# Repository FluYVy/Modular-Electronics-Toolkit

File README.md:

# Modular-Electronics-Toolkit

This project is a diploma thesis done at the [HTL Rankweil](https://github.com/htl-rankweil). It aims to provide future students with a better way to understand and work with different sensors and actuators. The system created aims to be modular so that different parts of it can be mixed to create new and creative projects. Different libraries are also provided to help students use these modules.

To further help with the development of different projects, a visual coding engine can be used to create the needed code. This is done with [Blockly](https://developers.google.com/blockly), which was developed by Google.

## Key Features
### Compability
The modules created should be compatible with any microcontroller, as long as they can handle 5 volts.

> [!WARNING]
> The provided code and libraries have only been tested with a board using the ATMEGA16A-Chip. For other microcontrollers, you may need to create your own code.

### Modular
The modules are designed to be able to create new projects by combining them together. As such, even complex problems can be solved easily.

### Easy to use
The libraries are designed to be used by students and as such are easy to use and adapt to your project or solution. This is reinforced by the block-based code editor for easy project creation. 

## Used Software and Libraries
* [Microchip Studio](https://www.microchip.com/en-us/tools-resources/develop/microchip-studio) for programming the libraries
* [KiCad](https://www.kicad.org/) for creating the modules
* [Blockly](https://developers.google.com/blockly) as a library for the blocks-based code editor

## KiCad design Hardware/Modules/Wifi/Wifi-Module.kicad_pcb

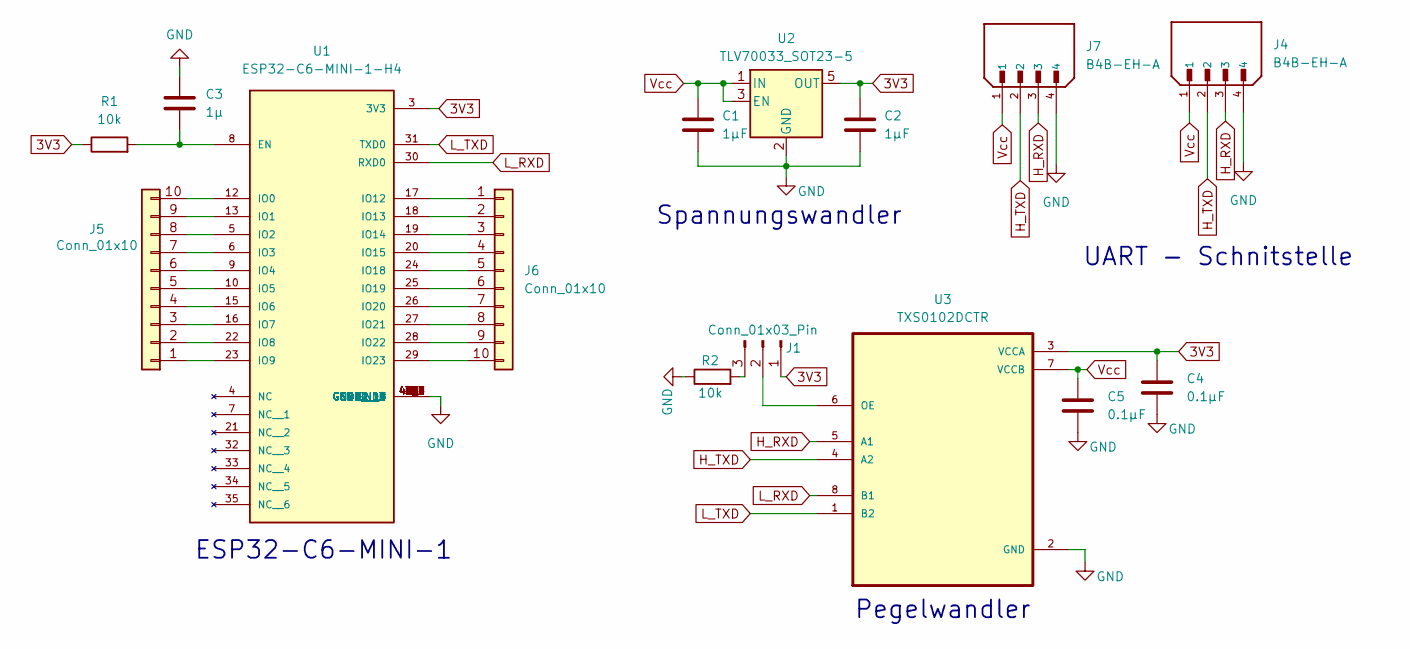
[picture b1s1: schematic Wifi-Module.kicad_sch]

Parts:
C1, C2: 1µF; C_0603_1608Metric_Pad1.08x0.95mm_HandSolder
C3: 1µ; C_0603_1608Metric_Pad1.08x0.95mm_HandSolder
C4, C5: 0.1µF; C_0603_1608Metric_Pad1.08x0.95mm_HandSolder
J1: Conn_01x03_Pin; PinHeader_1x03_P2.54mm_Vertical
J4, J7: B4B-EH-A; JST_B4B-EH-A
J5, J6: Conn_01x10; PinHeader_1x10_P2.54mm_Vertical
R1, R2: 10k; R_0603_1608Metric_Pad0.98x0.95mm_HandSolder
U1: ESP32-C6-MINI-1-H4; XCVR_ESP32-C6-MINI-1-H4; PARTREV 1.0
U2: TLV70033_SOT23-5; SOT-23-5
U3: TXS0102DCTR

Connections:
3V3: C2.1, C4.2, J1.1, R1.1, U1.3 (3V3), U2.5 (OUT), U3.3 (VCCA)
GND: C1.2, C2.2, C3.1, C4.1, C5.1, J4.4, J7.4, R2.1, U1.1 (GND1), U1.2 (GND1__1), U1.11 (GND1__2), U1.14 (GND1__3), U1.36 (GND1__4), U1.37 (GND1__5), U1.38 (GND1__6), U1.39 (GND1__7), U1.40 (GND1__8), U1.41 (GND1__9), U1.42 (GND1__10), U1.43 (GND1__11), U1.44 (GND1__12), U1.45 (GND1__13), U1.46 (GND1__14), U1.47 (GND2), U1.48 (GND2__1), U1.49_1 (GND2__2), U1.49_2 (GND2__3), U1.49_3 (GND2__4), U1.49_4 (GND2__5), U1.49_5 (GND2__6), U1.49_6 (GND2__7), U1.49_7 (GND2__8), U1.49_8 (GND2__9), U1.49_9 (GND2__10), U1.50 (GND2__11), U1.51 (GND2__12), U1.52 (GND2__13), U1.53 (GND2__14), U2.2 (GND), U3.2 (GND)
H_RXD: J4.3, J7.3, U3.5 (A1)
H_TXD: J4.2, J7.2, U3.4 (A2)
L_RXD: U1.30 (RXD0), U3.8 (B1)
L_TXD: U1.31 (TXD0), U3.1 (B2)
unnamed: J1.2, U3.6 (OE)
unnamed: J1.3, R2.2
unnamed: J5.1, U1.23 (IO9)
unnamed: J5.2, U1.22 (IO8)
unnamed: J5.3, U1.16 (IO7)
unnamed: J5.4, U1.15 (IO6)
unnamed: J5.5, U1.10 (IO5)
unnamed: J5.6, U1.9 (IO4)
unnamed: J5.7, U1.6 (IO3)
unnamed: J5.8, U1.5 (IO2)
unnamed: J5.9, U1.13 (IO1)
unnamed: J5.10, U1.12 (IO0)
unnamed: J6.1, U1.17 (IO12)
unnamed: J6.2, U1.18 (IO13)
unnamed: J6.3, U1.19 (IO14)
unnamed: J6.4, U1.20 (IO15)
unnamed: J6.5, U1.24 (IO18)
unnamed: J6.6, U1.25 (IO19)
unnamed: J6.7, U1.26 (IO20)
unnamed: J6.8, U1.27 (IO21)
unnamed: J6.9, U1.28 (IO22)
unnamed: J6.10, U1.29 (IO23)
unnamed: C3.2, R1.2, U1.8 (EN)
Vcc: C1.1, C5.2, J4.1, J7.1, U2.1 (IN), U2.3 (EN), U3.7 (VCCB)

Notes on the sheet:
UART - Schnitstelle
ESP32-C6-MINI-1
Pegelwandler
Spannungswandler

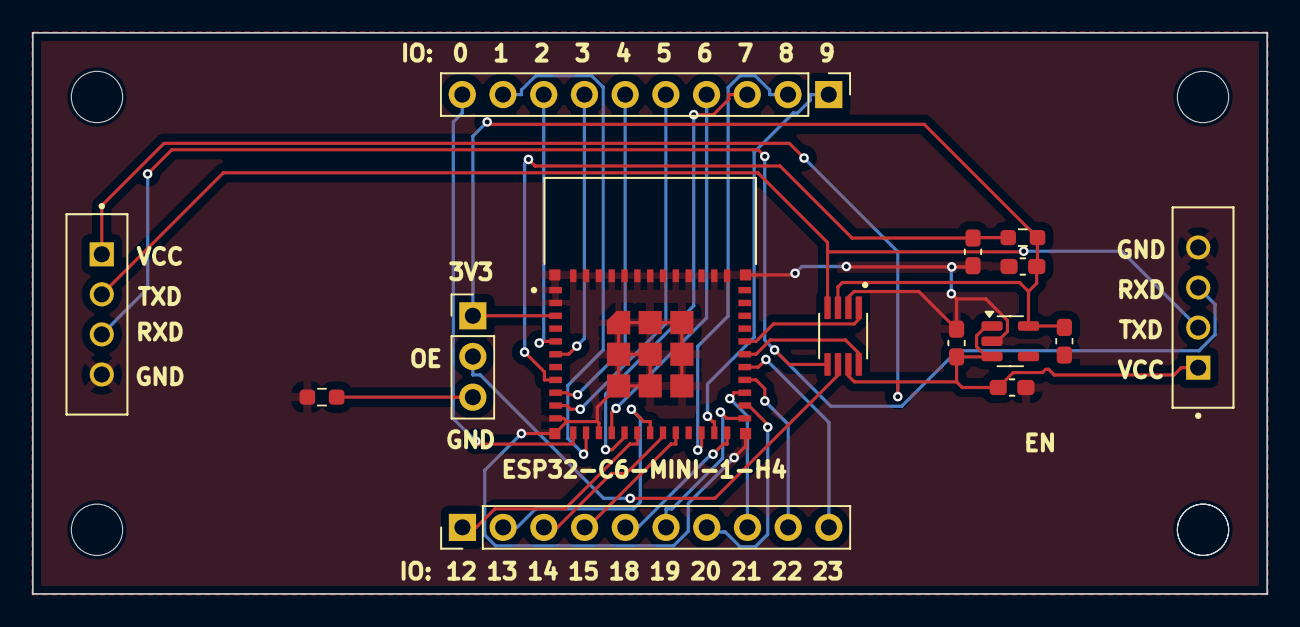
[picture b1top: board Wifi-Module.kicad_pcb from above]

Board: 2 copper layers, 77.0 x 35.0 mm, 15 parts (0 on the bottom side), 30 nets.

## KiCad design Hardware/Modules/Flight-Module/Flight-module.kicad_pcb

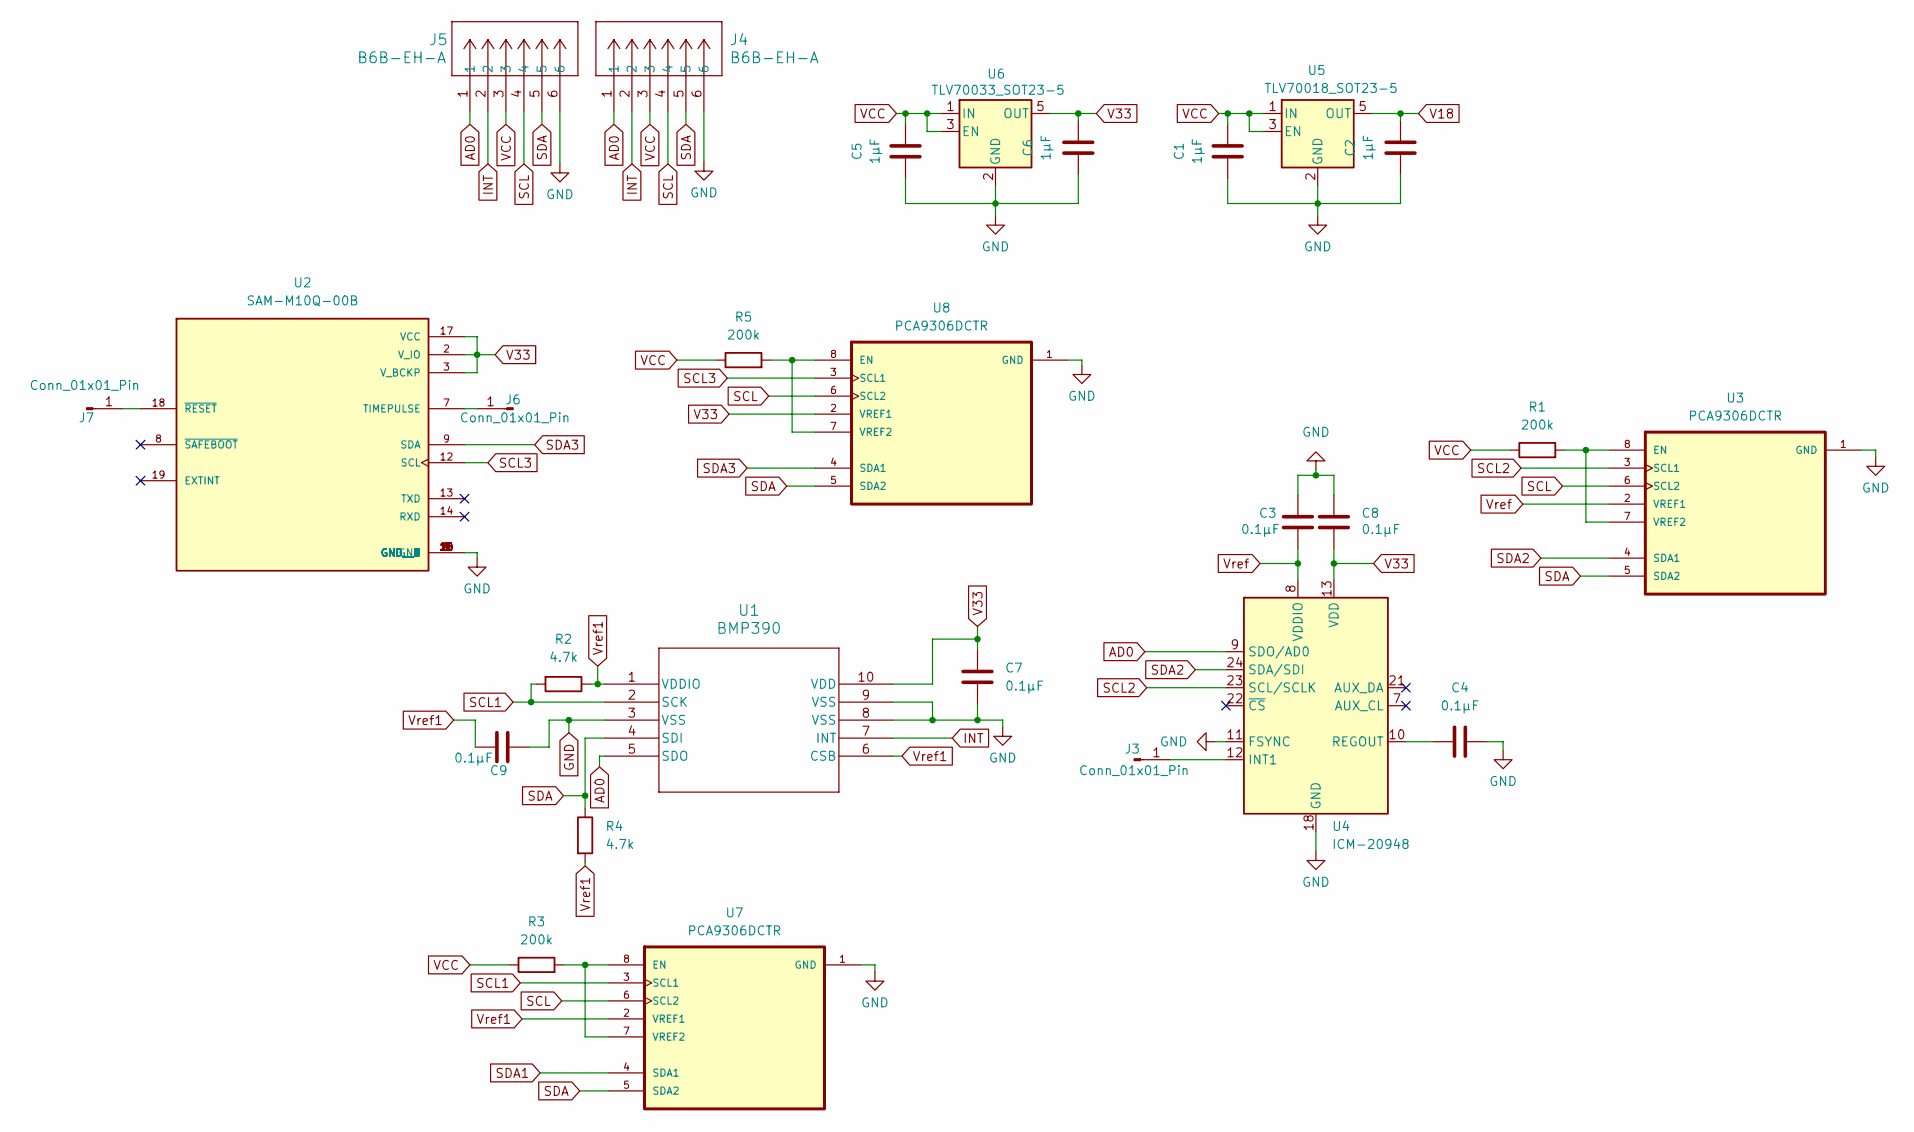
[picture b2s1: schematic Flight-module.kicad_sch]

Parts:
C1, C2, C5, C6: 1µF; C_0603_1608Metric
C3, C4, C7, C8, C9: 0.1µF; C_0603_1608Metric
J3, J6, J7: Conn_01x01_Pin; PinHeader_1x01_P2.54mm_Vertical
J4, J5: B6B-EH-A; JST_EH_B6B-EH-A_1x06_P2.50mm_Vertical
R1, R3, R5: 200k; R_0603_1608Metric
R2, R4: 4.7k; R_0603_1608Metric
U1: BMP390; 10LGA_2X2X0p75_BOS
U2: SAM-M10Q-00B; XCVR_SAM-M10Q-00B; PARTREV R03
U3, U7, U8: PCA9306DCTR; SOP65P400X130-8N
U4: ICM-20948; InvenSense_QFN-24_3x3mm_P0.4mm
U5: TLV70018_SOT23-5; SOT-23-5
U6: TLV70033_SOT23-5; SOT-23-5

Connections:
AD0: J4.1, J5.1, U1.5 (SDO), U4.9 (SDO/AD0)
GND: C1.1, C2.1, C3.1, C4.2, C5.1, C6.1, C7.1, C8.1, C9.2, J4.6, J5.6, U1.3 (VSS), U1.8 (VSS), U1.9 (VSS), U2.1 (GND), U2.4 (GND__1), U2.5 (GND__2), U2.6 (GND__3), U2.10 (GND__4), U2.11 (GND__5), U2.15 (GND__6), U2.16 (GND__7), U2.20 (GND__8), U3.1 (GND), U4.11 (FSYNC), U4.18 (GND), U4.20 (GND), U5.2 (GND), U6.2 (GND), U7.1 (GND), U8.1 (GND)
INT: J4.2, J5.2, U1.7 (INT)
unnamed: J3.1, U4.12 (INT1)
unnamed: J6.1, U2.7 (TIMEPULSE)
unnamed: J7.1, U2.18 (~RESET)
unnamed: R1.2, U3.7 (VREF2), U3.8 (EN)
unnamed: C4.1, U4.10 (REGOUT)
unnamed: R3.2, U7.7 (VREF2), U7.8 (EN)
unnamed: R5.2, U8.7 (VREF2), U8.8 (EN)
SCL: J4.4, J5.4, U3.6 (SCL2), U7.6 (SCL2), U8.6 (SCL2)
SCL1: R2.2, U1.2 (SCK), U7.3 (SCL1)
SCL2: U3.3 (SCL1), U4.23 (SCL/SCLK)
SCL3: U2.12 (SCL), U8.3 (SCL1)
SDA: J4.5, J5.5, R4.1, U1.4 (SDI), U3.5 (SDA2), U7.5 (SDA2), U8.5 (SDA2)
SDA1: U7.4 (SDA1)
SDA2: U3.4 (SDA1), U4.24 (SDA/SDI)
SDA3: U2.9 (SDA), U8.4 (SDA1)
V18: C2.2, U5.5 (OUT)
V33: C6.2, C7.2, C8.2, U1.10 (VDD), U2.2 (V_IO), U2.3 (V_BCKP), U2.17 (VCC), U4.13 (VDD), U6.5 (OUT), U8.2 (VREF1)
VCC: C1.2, C5.2, J4.3, J5.3, R1.1, R3.1, R5.1, U5.1 (IN), U5.3 (EN), U6.1 (IN), U6.3 (EN)
Vref: C3.2, U3.2 (VREF1), U4.8 (VDDIO)
Vref1: C9.1, R2.1, R4.2, U1.1 (VDDIO), U1.6 (CSB), U7.2 (VREF1)

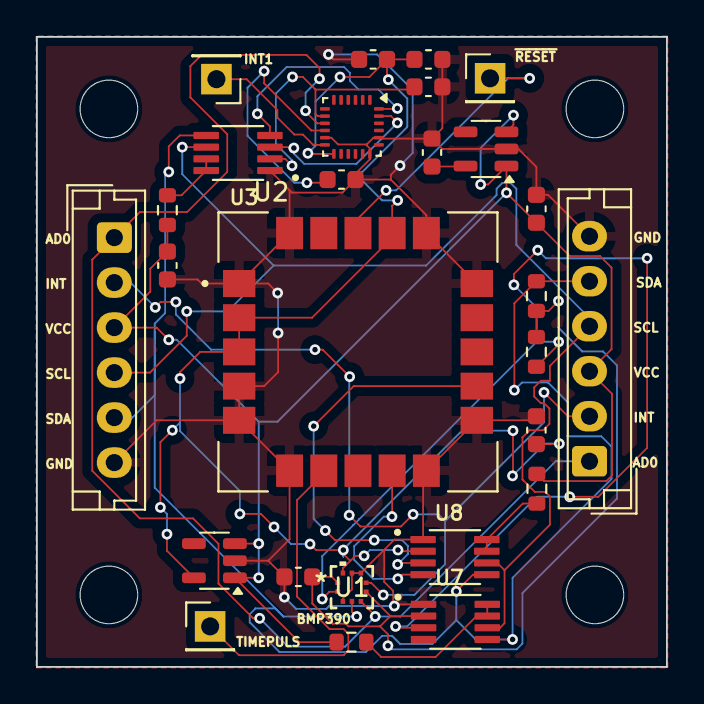
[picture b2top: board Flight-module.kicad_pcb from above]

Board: 2 copper layers, 35.0 x 35.0 mm, 27 parts (0 on the bottom side), 22 nets.

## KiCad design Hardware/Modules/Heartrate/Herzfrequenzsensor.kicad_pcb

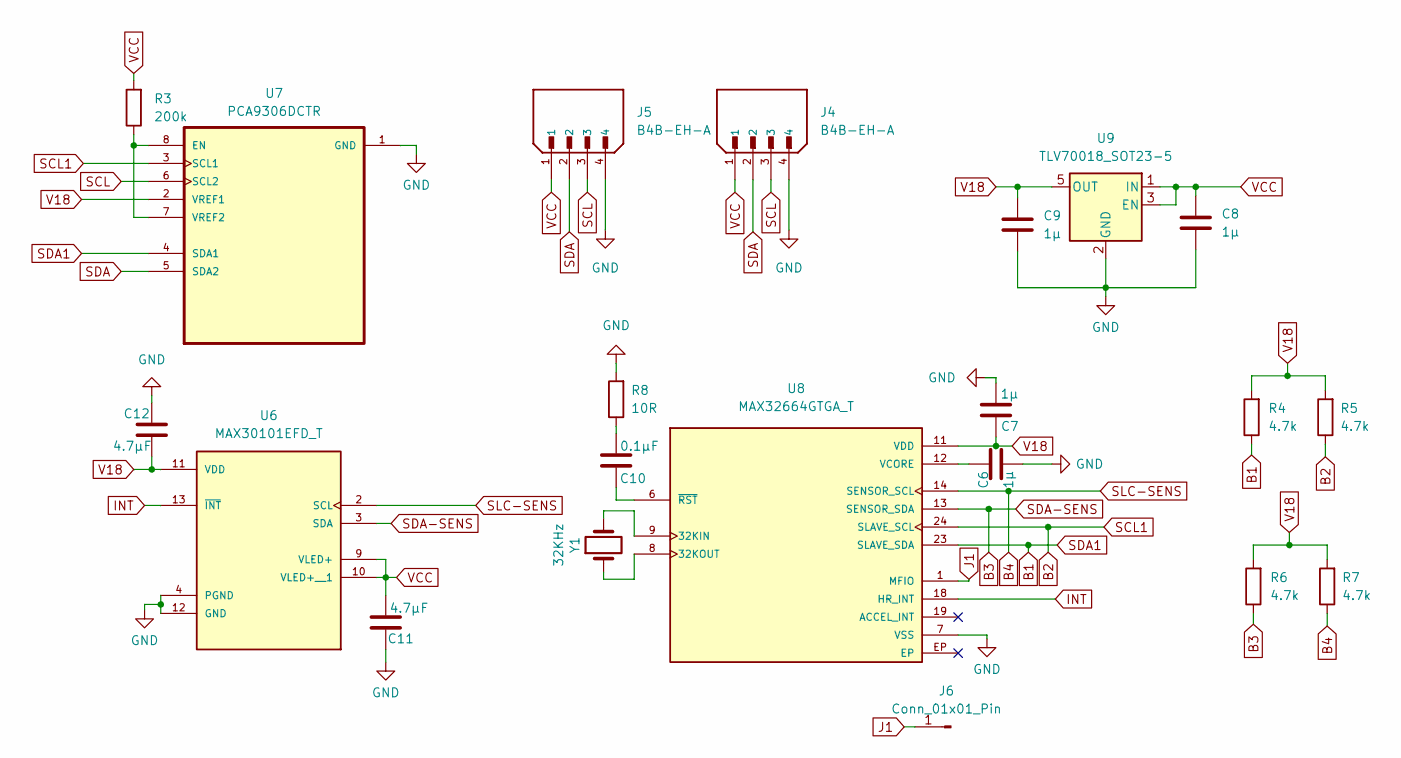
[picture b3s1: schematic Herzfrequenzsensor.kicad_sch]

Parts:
C6, C7, C8, C9: 1µ; C_0603_1608Metric_Pad1.08x0.95mm_HandSolder
C10: 0.1µF; C_0603_1608Metric_Pad1.08x0.95mm_HandSolder
C11, C12: 4.7µF; C_0603_1608Metric_Pad1.08x0.95mm_HandSolder
J4, J5: B4B-EH-A; JST_EH_B4B-EH-A_1x04_P2.50mm_Vertical
J6: Conn_01x01_Pin; PinHeader_1x01_P2.54mm_Vertical
R3: 200k; R_0603_1608Metric_Pad0.98x0.95mm_HandSolder
R4, R5, R6, R7: 4.7k; R_0603_1608Metric_Pad0.98x0.95mm_HandSolder
R8: 10R; R_0603_1608Metric_Pad0.98x0.95mm_HandSolder
U6: MAX30101EFD_T; PSON80P560X330X165-14N; PARTREV 2
U7: PCA9306DCTR; SOP65P400X130-8N
U8: MAX32664GTGA_T; IC_MAX32664GTGA_T; PARTREV 4
U9: TLV70018_SOT23-5; SOT-23-5
Y1: 32KHz; XTAL_CM7V-T1A-LOW-ESR-32.768KHZ-6PF-20-TA-QC

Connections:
B1: R4.1, U7.4 (SDA1), U8.23 (SLAVE_SDA)
B2: R5.1, U7.3 (SCL1), U8.24 (SLAVE_SCL)
B3: R6.1, U6.3 (SDA), U8.13 (SENSOR_SDA)
B4: R7.1, U6.2 (SCL), U8.14 (SENSOR_SCL)
GND: C6.1, C7.1, C8.2, C9.2, C11.2, C12.2, J4.4, J5.4, R8.2, U6.4 (PGND), U6.12 (GND), U7.1 (GND), U8.7 (VSS), U8.10 (VSS__1), U9.2 (GND)
INT: U6.13 (~INT), U8.18 (HR_INT)
J1: J6.1, U8.1 (MFIO)
unnamed: C10.1, R8.1
unnamed: R3.1, U7.7 (VREF2), U7.8 (EN)
unnamed: U8.9 (32KIN), Y1.2
unnamed: U8.8 (32KOUT), Y1.1
unnamed: C6.2, U8.12 (VCORE)
unnamed: C10.2, U8.6 (~RST)
SCL: J4.3, J5.3, U7.6 (SCL2)
SDA: J4.2, J5.2, U7.5 (SDA2)
V18: C7.2, C9.1, C12.1, R4.2, R5.2, R6.2, R7.2, U6.11 (VDD), U7.2 (VREF1), U8.11 (VDD), U8.22 (VDD__1), U9.5 (OUT)
VCC: C8.1, C11.1, J4.1, J5.1, R3.2, U6.9 (VLED+), U6.10 (VLED+__1), U9.1 (IN), U9.3 (EN)

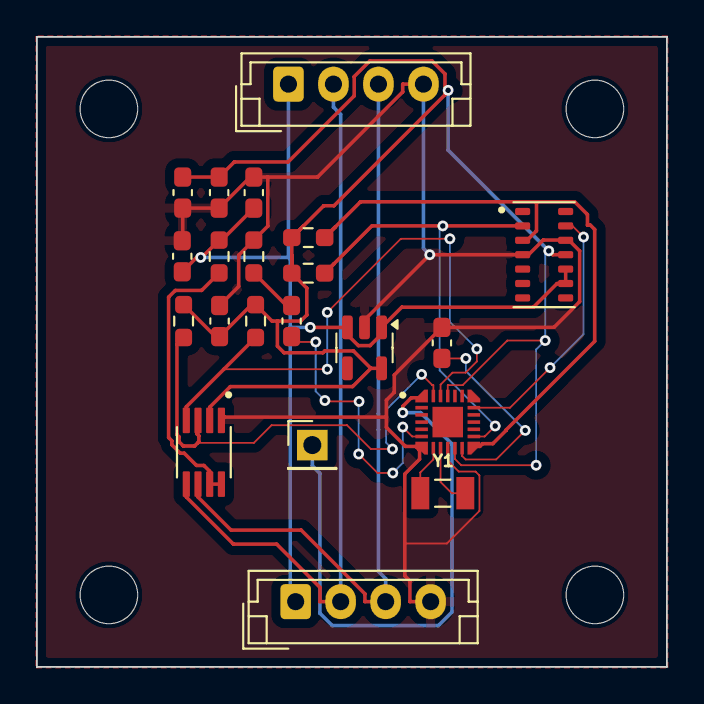
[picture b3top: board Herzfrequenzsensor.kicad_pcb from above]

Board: 2 copper layers, 35.0 x 35.0 mm, 21 parts (0 on the bottom side), 17 nets.

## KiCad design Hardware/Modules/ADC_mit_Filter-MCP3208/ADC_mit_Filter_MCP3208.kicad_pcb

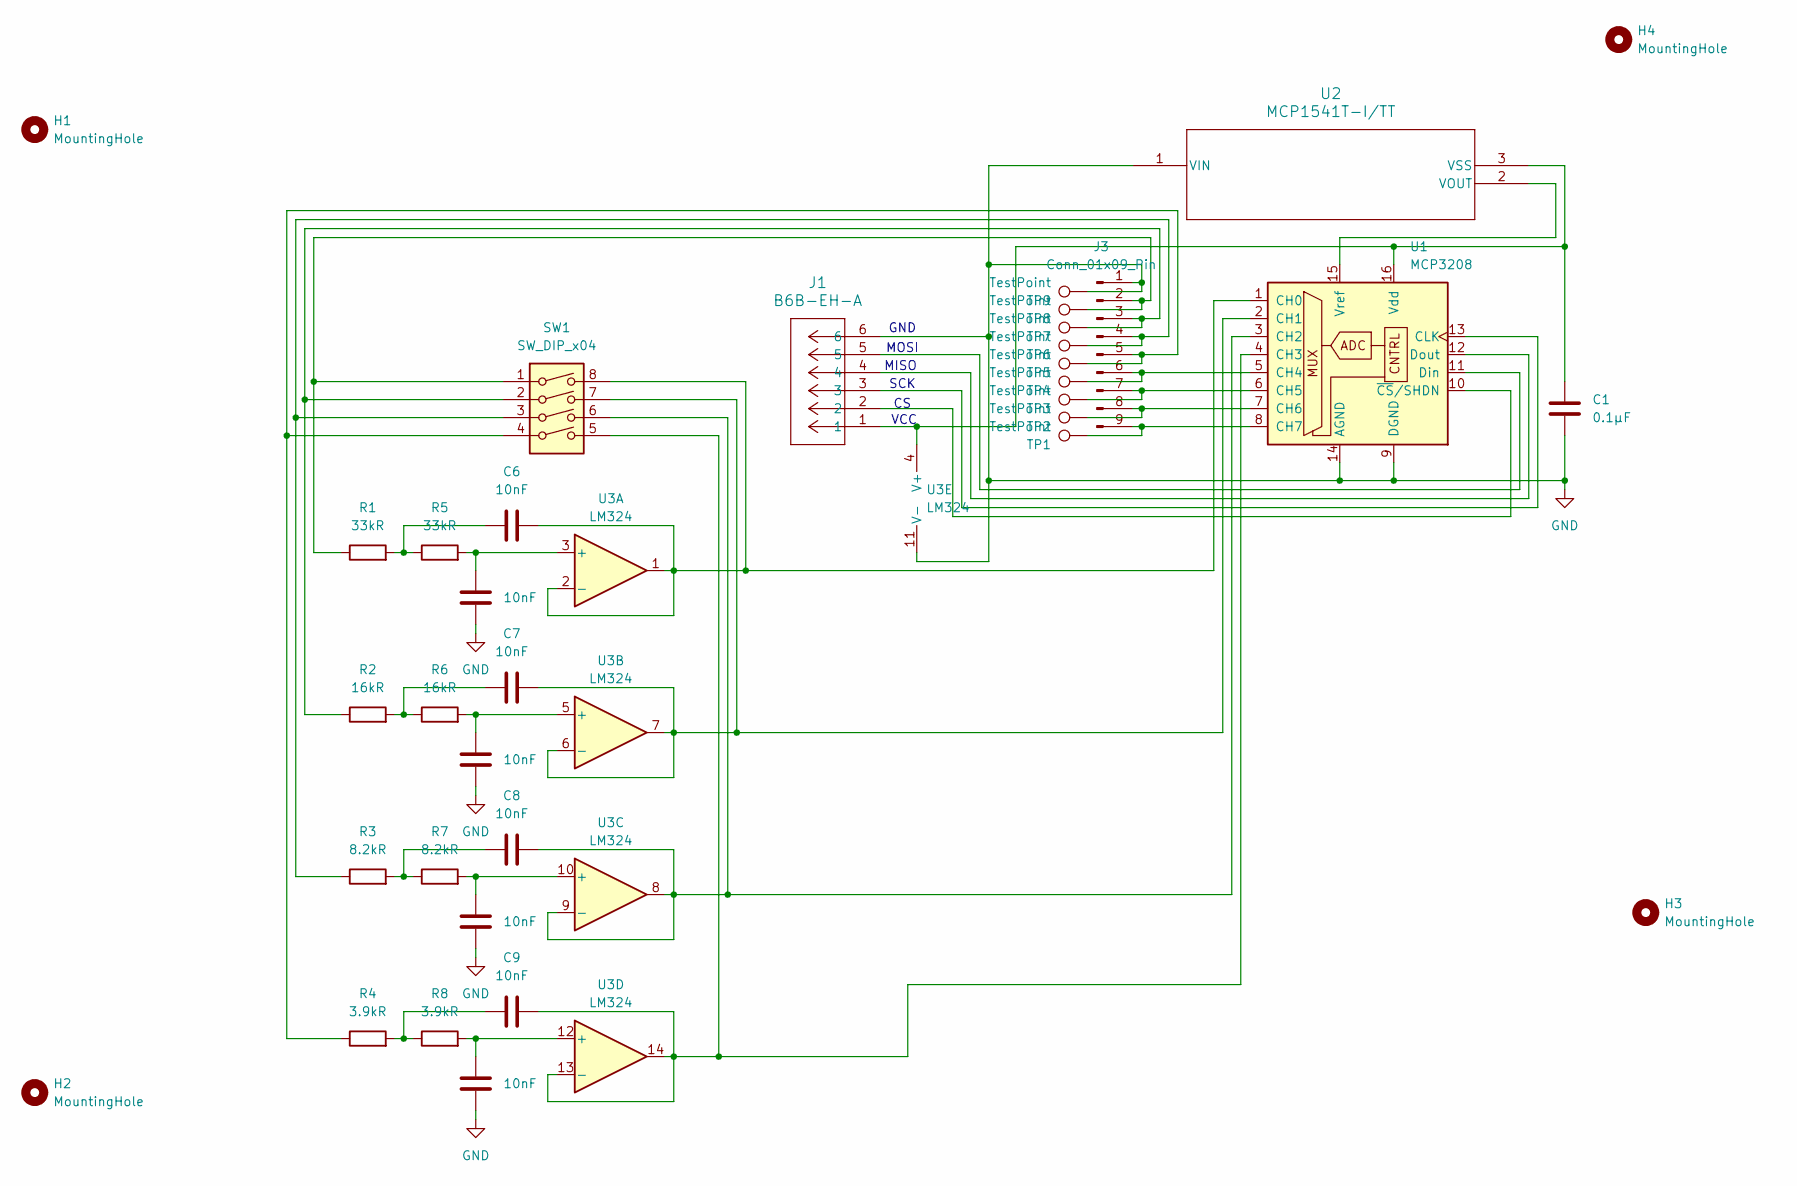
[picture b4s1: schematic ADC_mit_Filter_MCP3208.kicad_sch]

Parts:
C1: 0.1µF; C_0603_1608Metric_Pad1.08x0.95mm_HandSolder
C2, C3, C4, C5, C6, C7, C8, C9: 10nF; C_0603_1608Metric_Pad1.08x0.95mm_HandSolder
H1, H2, H3, H4: MountingHole; MountingHole_3.2mm_M3
J1: B6B-EH-A; JST_EH_B6B-EH-A_1x06_P2.50mm_Vertical
J3: Conn_01x09_Pin; PinHeader_1x09_P2.54mm_Vertical
R1, R5: 33kR; R_0603_1608Metric_Pad0.98x0.95mm_HandSolder
R2, R6: 16kR; R_0603_1608Metric_Pad0.98x0.95mm_HandSolder
R3, R7: 8.2kR; R_0603_1608Metric_Pad0.98x0.95mm_HandSolder
R4, R8: 3.9kR; R_0603_1608Metric_Pad0.98x0.95mm_HandSolder
SW1: SW_DIP_x04; SW_DIP_SPSTx04_Slide_9.78x12.34mm_W7.62mm_P2.54mm
TP1, TP2, TP3, TP4, TP5, TP6, TP7, TP8, TP9: TestPoint; TestPoint_Pad_1.0x1.0mm
U1: MCP3208; SOIC16-N_MC_MCH-M
U2: MCP1541T-I/TT; SOT-23_MC_MCH-M
U3: LM324; SOIC-14_3.9x8.7mm_P1.27mm

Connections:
GND: C1.2, C2.2, C3.2, C4.2, C5.2, J1.6, J3.1, TP9.1, U1.9 (DGND), U1.14 (AGND), U2.1 (VIN), U3.11 (V-)
unnamed: C6.1, R1.2, R5.1
unnamed: C7.1, R2.2, R6.1
unnamed: C8.1, R3.2, R7.1
unnamed: C9.1, R4.2, R8.1
unnamed: J3.2, R1.1, SW1.1, TP8.1
unnamed: J3.3, R2.1, SW1.2, TP7.1
unnamed: J3.4, R3.1, SW1.3, TP6.1
unnamed: J3.5, R4.1, SW1.4, TP5.1
unnamed: J3.6, TP4.1, U1.5 (CH4)
unnamed: J3.7, TP3.1, U1.6 (CH5)
unnamed: J3.8, TP2.1, U1.7 (CH6)
unnamed: J3.9, TP1.1, U1.8 (CH7)
unnamed: C6.2, SW1.8, U1.1 (CH0), U3.1, U3.2 (-)
unnamed: C7.2, SW1.7, U1.2 (CH1), U3.6 (-), U3.7
unnamed: C8.2, SW1.6, U1.3 (CH2), U3.8, U3.9 (-)
unnamed: C9.2, SW1.5, U1.4 (CH3), U3.13 (-), U3.14
unnamed: J1.3, U1.13 (CLK)
unnamed: J1.5, U1.11 (Din)
unnamed: J1.4, U1.12 (Dout)
unnamed: C1.1, J1.1, U1.16 (Vdd), U2.3 (VSS), U3.4 (V+)
unnamed: U1.15 (Vref), U2.2 (VOUT)
unnamed: J1.2, U1.10 (~CS/SHDN)
unnamed: C2.1, R5.2, U3.3 (+)
unnamed: C3.1, R6.2, U3.5 (+)
unnamed: C4.1, R7.2, U3.10 (+)
unnamed: C5.1, R8.2, U3.12 (+)

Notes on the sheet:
VCC
MISO
SCK
GND
MOSI

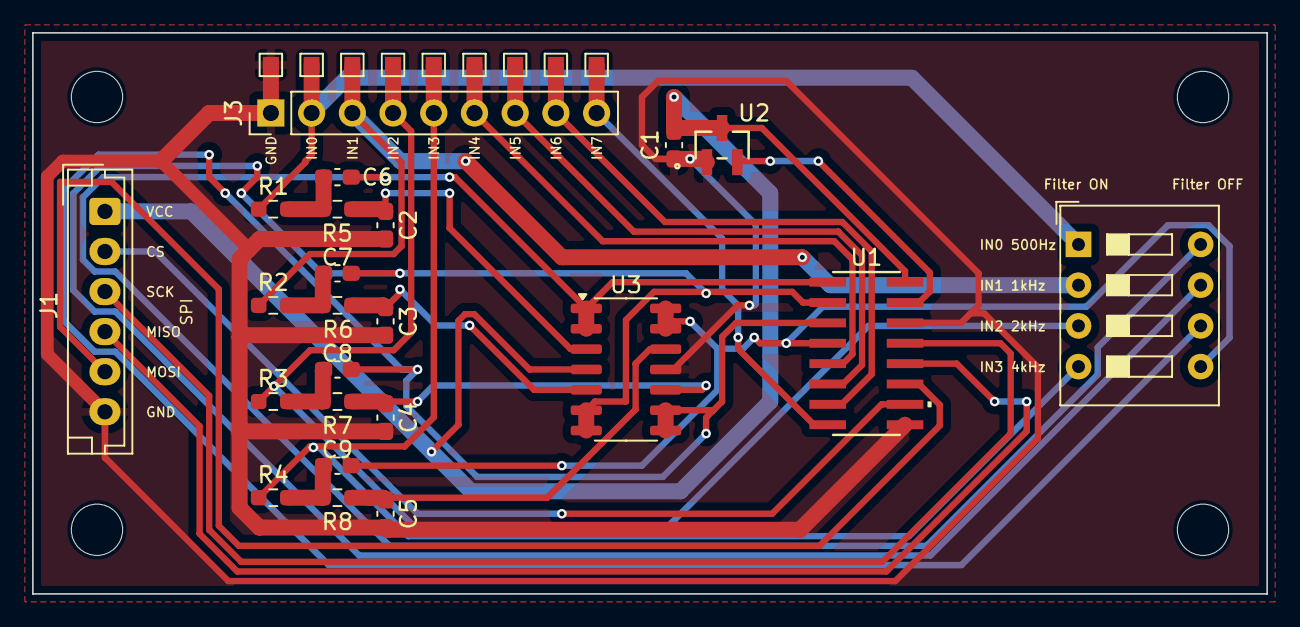
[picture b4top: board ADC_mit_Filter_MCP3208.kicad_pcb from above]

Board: 2 copper layers, 77.0 x 35.0 mm, 36 parts (0 on the bottom side), 27 nets.

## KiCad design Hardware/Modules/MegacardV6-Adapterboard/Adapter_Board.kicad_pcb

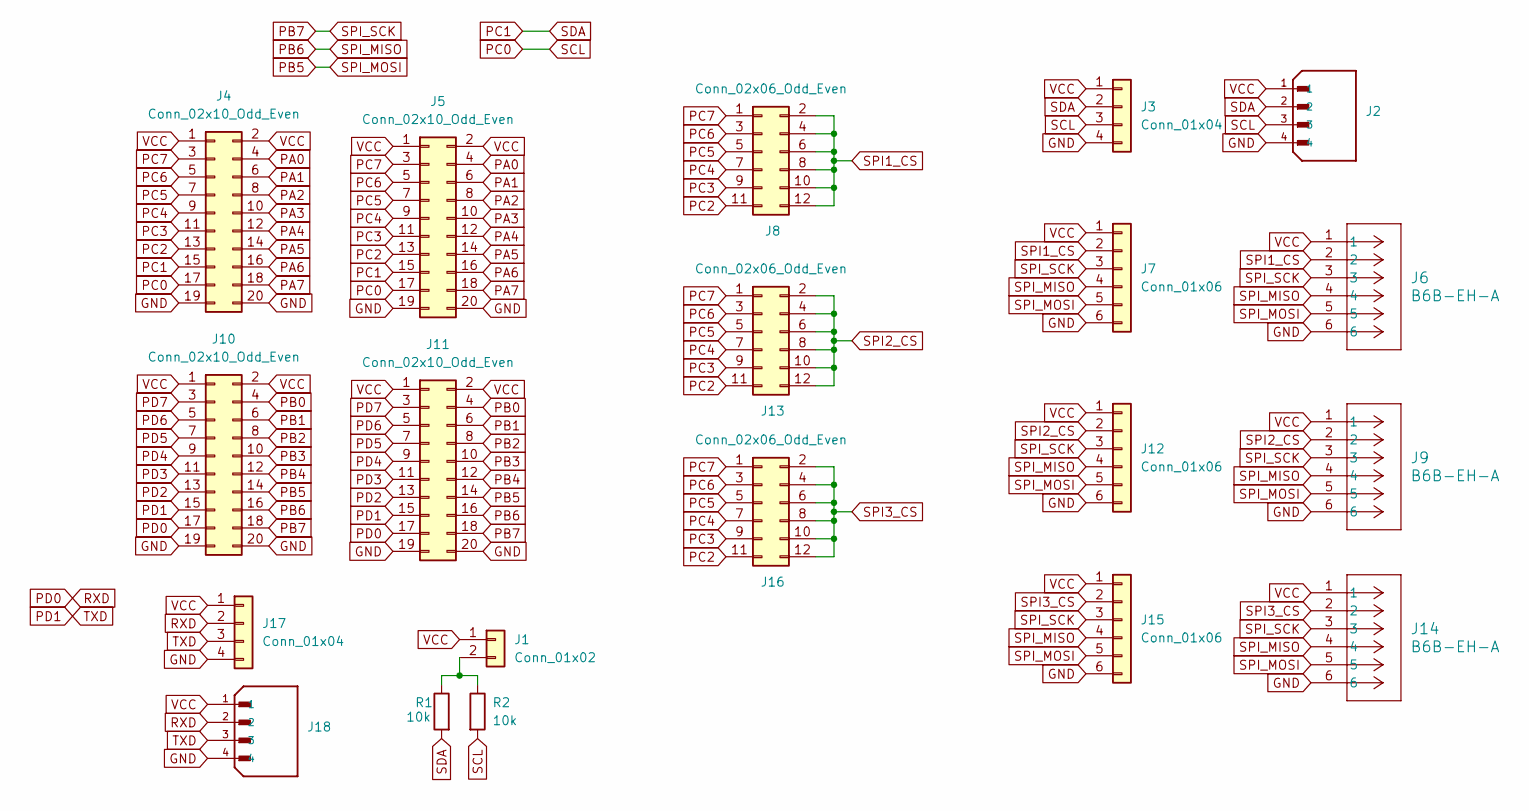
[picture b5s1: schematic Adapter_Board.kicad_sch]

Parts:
J1: Conn_01x02; PinHeader_1x02_P2.54mm_Vertical
J2, J18: JST_EH_B4B-EH-A_1x04_P2.50mm_Vertical
J3, J17: Conn_01x04; PinSocket_1x04_P2.54mm_Vertical
J4, J10: Conn_02x10_Odd_Even; PinSocket_2x10_P2.54mm_Horizontal
J5, J11: Conn_02x10_Odd_Even; PinSocket_2x10_P2.54mm_Vertical
J6, J9, J14: B6B-EH-A; CONN_B6B-EH-A_JST
J7, J12, J15: Conn_01x06; PinHeader_1x06_P2.54mm_Vertical
J8, J13, J16: Conn_02x06_Odd_Even; PinHeader_2x06_P2.54mm_Vertical
R1, R2: 10k; R_0805_2012Metric

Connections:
GND: J2.4, J3.4, J4.19, J4.20, J5.19, J5.20, J6.6, J7.6, J9.6, J10.19, J10.20, J11.19, J11.20, J12.6, J14.6, J15.6, J17.4, J18.4
unnamed: J1.2, R1.1, R2.1
PA0: J4.4, J5.4
PA1: J4.6, J5.6
PA2: J4.8, J5.8
PA3: J4.10, J5.10
PA4: J4.12, J5.12
PA5: J4.14, J5.14
PA6: J4.16, J5.16
PA7: J4.18, J5.18
PB0: J10.4, J11.4
PB1: J10.6, J11.6
PB2: J10.8, J11.8
PB3: J10.10, J11.10
PB4: J10.12, J11.12
PB5: J6.5, J7.5, J9.5, J10.14, J11.14, J12.5, J14.5, J15.5
PB6: J6.4, J7.4, J9.4, J10.16, J11.16, J12.4, J14.4, J15.4
PB7: J6.3, J7.3, J9.3, J10.18, J11.18, J12.3, J14.3, J15.3
PC0: J2.3, J3.3, J4.17, J5.17, R2.2
PC1: J2.2, J3.2, J4.15, J5.15, R1.2
PC2: J4.13, J5.13, J8.11, J13.11, J16.11
PC3: J4.11, J5.11, J8.9, J13.9, J16.9
PC4: J4.9, J5.9, J8.7, J13.7, J16.7
PC5: J4.7, J5.7, J8.5, J13.5, J16.5
PC6: J4.5, J5.5, J8.3, J13.3, J16.3
PC7: J4.3, J5.3, J8.1, J13.1, J16.1
PD0: J10.17, J11.17, J17.2, J18.2
PD1: J10.15, J11.15, J17.3, J18.3
PD2: J10.13, J11.13
PD3: J10.11, J11.11
PD4: J10.9, J11.9
PD5: J10.7, J11.7
PD6: J10.5, J11.5
PD7: J10.3, J11.3
SPI1_CS: J6.2, J7.2, J8.2, J8.4, J8.6, J8.8, J8.10, J8.12
SPI2_CS: J9.2, J12.2, J13.2, J13.4, J13.6, J13.8, J13.10, J13.12
SPI3_CS: J14.2, J15.2, J16.2, J16.4, J16.6, J16.8, J16.10, J16.12
VCC: J1.1, J2.1, J3.1, J4.1, J4.2, J5.1, J5.2, J6.1, J7.1, J9.1, J10.1, J10.2, J11.1, J11.2, J12.1, J14.1, J15.1, J17.1, J18.1

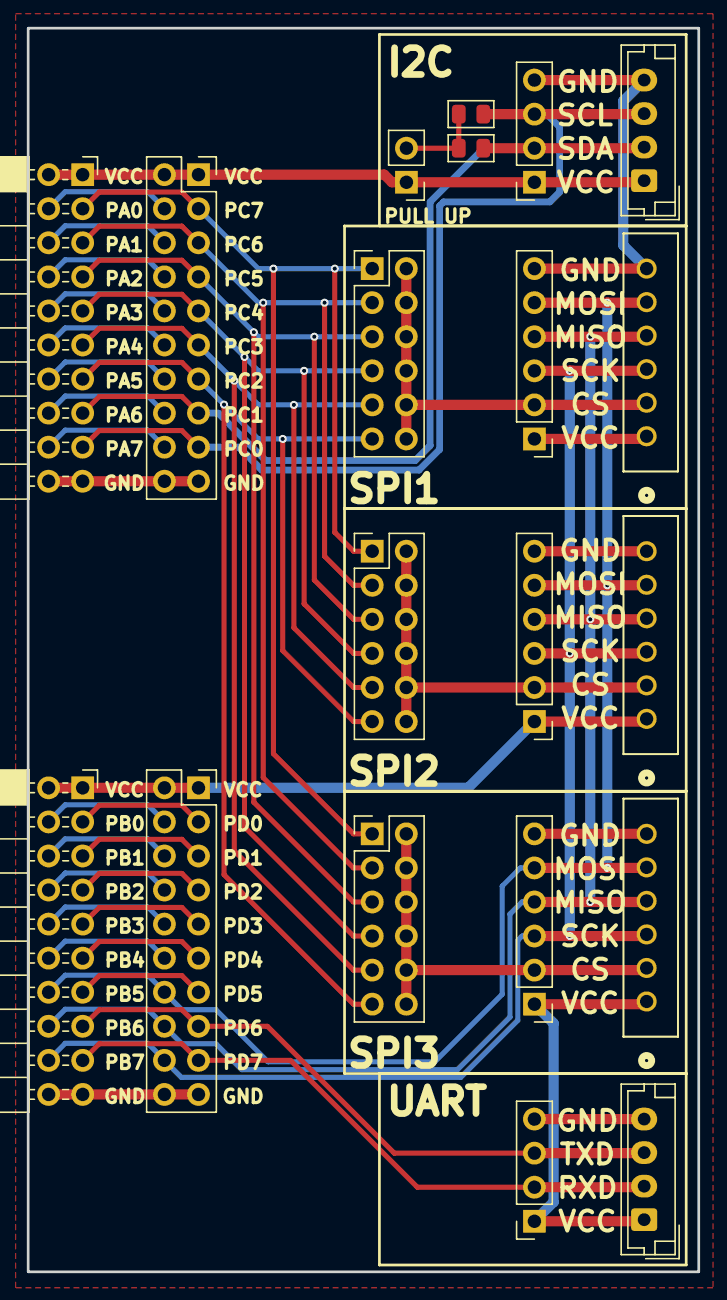
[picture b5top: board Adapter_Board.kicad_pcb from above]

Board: 2 copper layers, 50.0 x 92.7 mm, 20 parts (0 on the bottom side), 38 nets.

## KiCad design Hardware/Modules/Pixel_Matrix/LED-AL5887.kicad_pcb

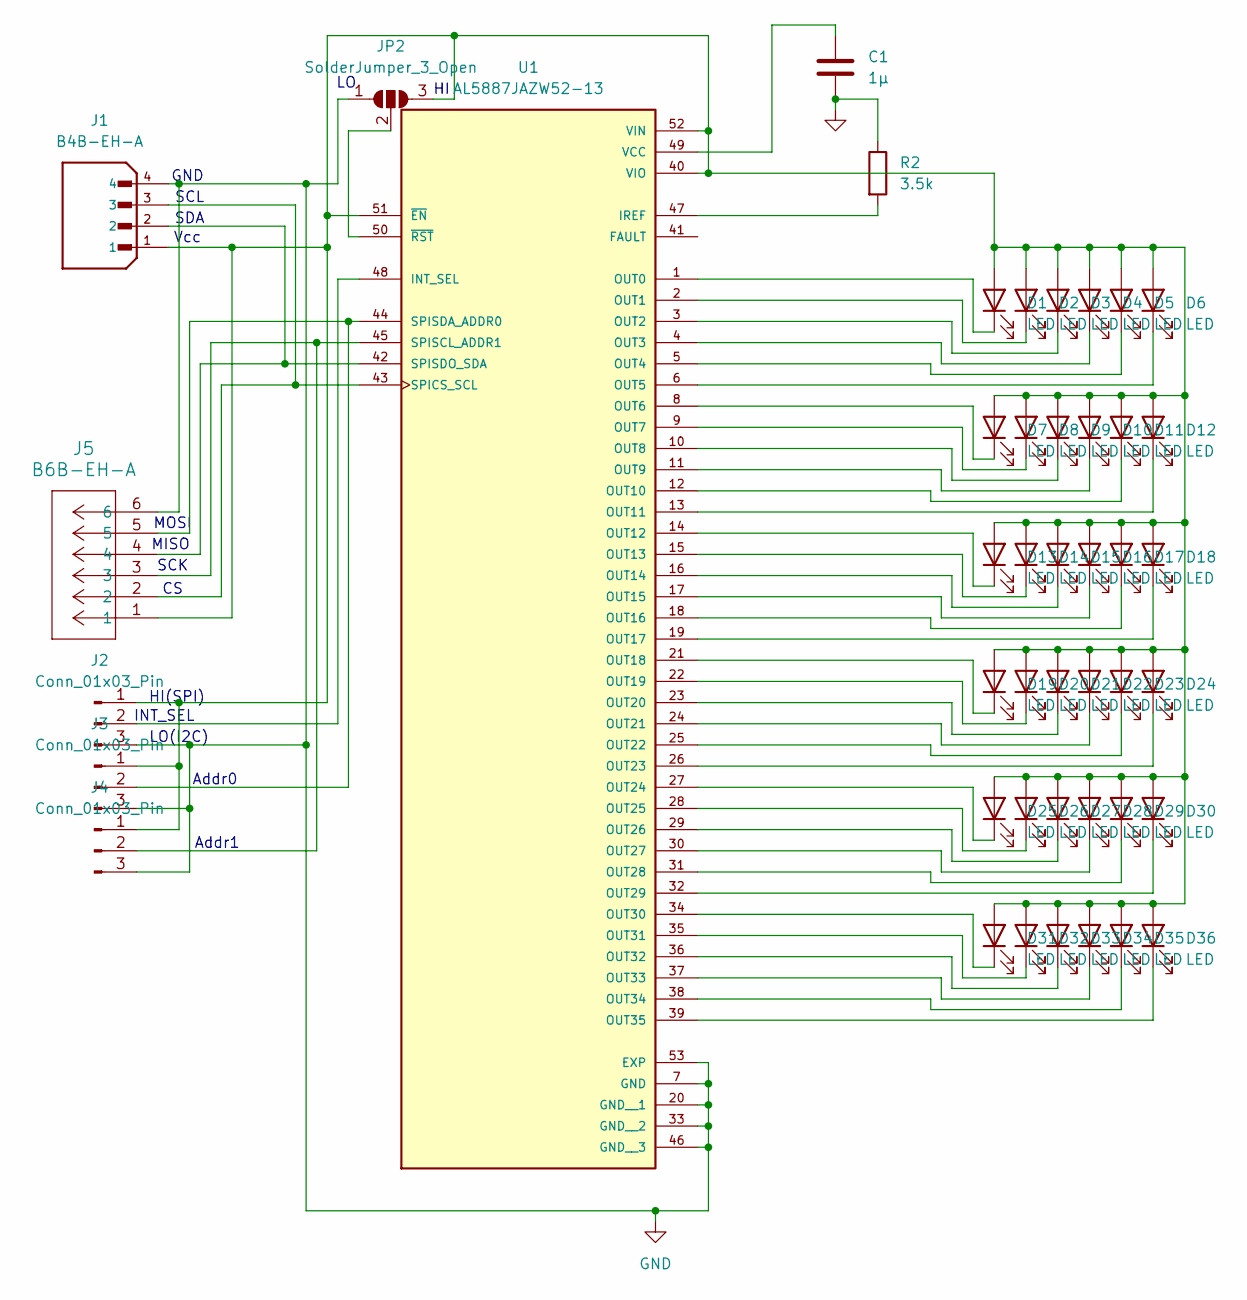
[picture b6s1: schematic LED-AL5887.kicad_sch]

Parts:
C1: 1µ; C_0603_1608Metric_Pad1.08x0.95mm_HandSolder
D1, D2, D3, D4, D5, D6, D7, D8, D9, D10, D11, D12, D13, D14, D15, D16, D17, D18, D19, D20, D21, D22, D23, D24, D25, D26, D27, D28, D29, D30, D31, D32, D33, D34, D35, D36: LED; LED_0603_1608Metric_Pad1.05x0.95mm_HandSolder
J1: B4B-EH-A; JST_EH_B4B-EH-A_1x04_P2.50mm_Vertical
J2, J3, J4: Conn_01x03_Pin; PinHeader_1x03_P2.54mm_Vertical
J5: B6B-EH-A; JST_EH_B6B-EH-A_1x06_P2.50mm_Vertical
JP2: SolderJumper_3_Open; SolderJumper-3_P2.0mm_Open_TrianglePad1.0x1.5mm
R2: 3.5k; R_0603_1608Metric_Pad0.98x0.95mm_HandSolder
U1: AL5887JAZW52-13; IC_AL5887JAZW52-13; PARTREV 4-2

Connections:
GND: C1.2, J1.4, J2.3, J3.3, J4.3, J5.6, JP2.1 (A), R2.1, U1.7 (GND), U1.20 (GND__1), U1.33 (GND__2), U1.46 (GND__3), U1.53 (EXP)
unnamed: D1.2 (A), D2.2 (A), D3.2 (A), D4.2 (A), D5.2 (A), D6.2 (A), D7.2 (A), D8.2 (A), D9.2 (A), D10.2 (A), D11.2 (A), D12.2 (A), D13.2 (A), D14.2 (A), D15.2 (A), D16.2 (A), D17.2 (A), D18.2 (A), D19.2 (A), D20.2 (A), D21.2 (A), D22.2 (A), D23.2 (A), D24.2 (A), D25.2 (A), D26.2 (A), D27.2 (A), D28.2 (A), D29.2 (A), D30.2 (A), D31.2 (A), D32.2 (A), D33.2 (A), D34.2 (A), D35.2 (A), D36.2 (A), J1.1, J2.1, J3.1, J4.1, J5.1, JP2.3 (B), U1.40 (VIO), U1.51 (~EN), U1.52 (VIN)
unnamed: D1.1 (K), U1.1 (OUT0)
unnamed: D2.1 (K), U1.2 (OUT1)
unnamed: D3.1 (K), U1.3 (OUT2)
unnamed: D4.1 (K), U1.4 (OUT3)
unnamed: D5.1 (K), U1.5 (OUT4)
unnamed: D6.1 (K), U1.6 (OUT5)
unnamed: D7.1 (K), U1.8 (OUT6)
unnamed: D8.1 (K), U1.9 (OUT7)
unnamed: D9.1 (K), U1.10 (OUT8)
unnamed: D10.1 (K), U1.11 (OUT9)
unnamed: D11.1 (K), U1.12 (OUT10)
unnamed: D12.1 (K), U1.13 (OUT11)
unnamed: D13.1 (K), U1.14 (OUT12)
unnamed: D14.1 (K), U1.15 (OUT13)
unnamed: D15.1 (K), U1.16 (OUT14)
unnamed: D16.1 (K), U1.17 (OUT15)
unnamed: D17.1 (K), U1.18 (OUT16)
unnamed: D18.1 (K), U1.19 (OUT17)
unnamed: D19.1 (K), U1.21 (OUT18)
unnamed: D20.1 (K), U1.22 (OUT19)
unnamed: D21.1 (K), U1.23 (OUT20)
unnamed: D22.1 (K), U1.24 (OUT21)
unnamed: D23.1 (K), U1.25 (OUT22)
unnamed: D24.1 (K), U1.26 (OUT23)
unnamed: D25.1 (K), U1.27 (OUT24)
unnamed: D26.1 (K), U1.28 (OUT25)
unnamed: D27.1 (K), U1.29 (OUT26)
unnamed: D28.1 (K), U1.30 (OUT27)
unnamed: D29.1 (K), U1.31 (OUT28)
unnamed: D30.1 (K), U1.32 (OUT29)
unnamed: D31.1 (K), U1.34 (OUT30)
unnamed: D32.1 (K), U1.35 (OUT31)
unnamed: D33.1 (K), U1.36 (OUT32)
unnamed: D34.1 (K), U1.37 (OUT33)
unnamed: D35.1 (K), U1.38 (OUT34)
unnamed: D36.1 (K), U1.39 (OUT35)
unnamed: J2.2, U1.48 (INT_SEL)
unnamed: J3.2, J5.5, U1.44 (SPISDA_ADDR0)
unnamed: J4.2, J5.3, U1.45 (SPISCL_ADDR1)
unnamed: JP2.2 (C), U1.50 (~RST)
unnamed: R2.2, U1.47 (IREF)
unnamed: J1.3, J5.2, U1.43 (SPICS_SCL)
unnamed: J1.2, J5.4, U1.42 (SPISDO_SDA)
unnamed: C1.1, U1.49 (VCC)

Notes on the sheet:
MISO
SCK
Vcc
SDA
SCL
Addr0
LO(I2C)
INT_SEL
HI(SPI)
Addr1
GND
MOSI

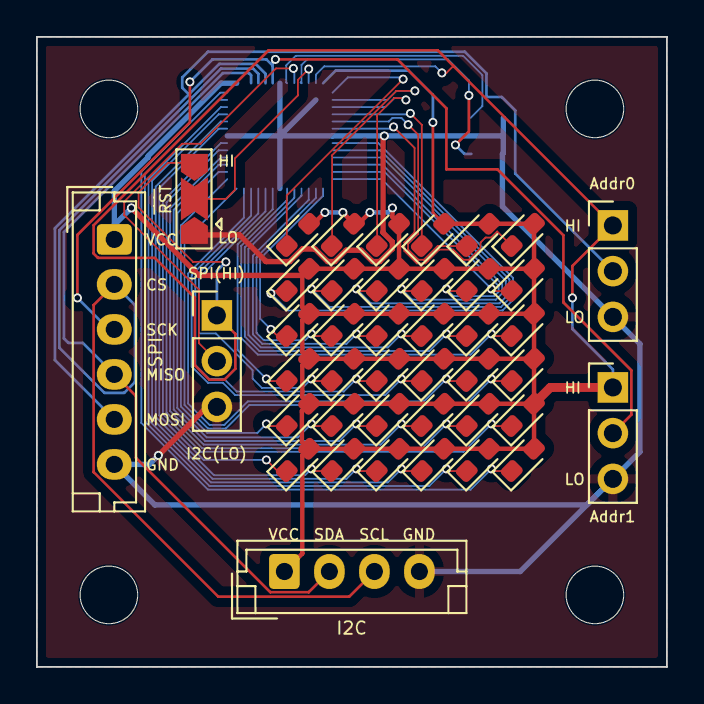
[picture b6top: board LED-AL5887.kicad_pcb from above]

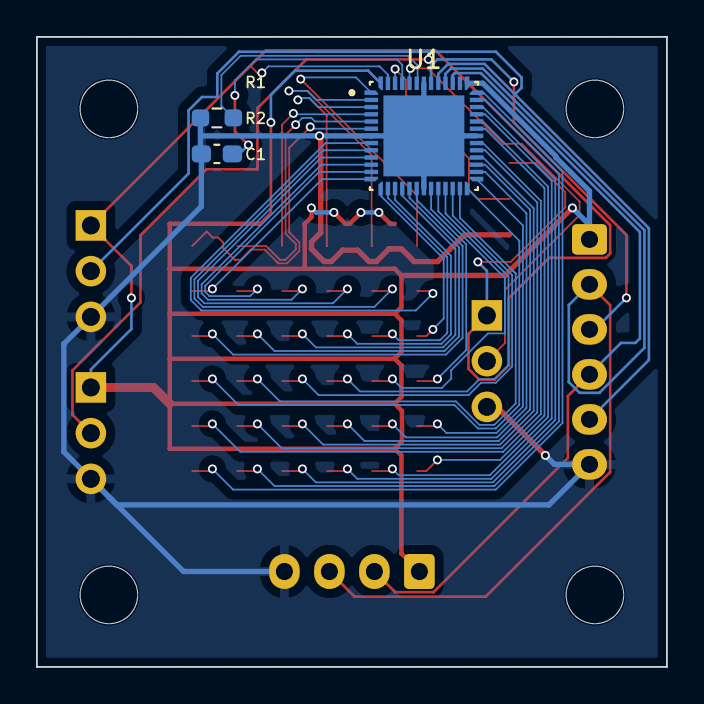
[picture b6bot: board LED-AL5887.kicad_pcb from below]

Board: 2 copper layers, 35.0 x 35.0 mm, 49 parts (3 on the bottom side), 46 nets.

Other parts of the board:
MH1, MH2, MH3, MH4: MountingHole_3.2mm_M3
